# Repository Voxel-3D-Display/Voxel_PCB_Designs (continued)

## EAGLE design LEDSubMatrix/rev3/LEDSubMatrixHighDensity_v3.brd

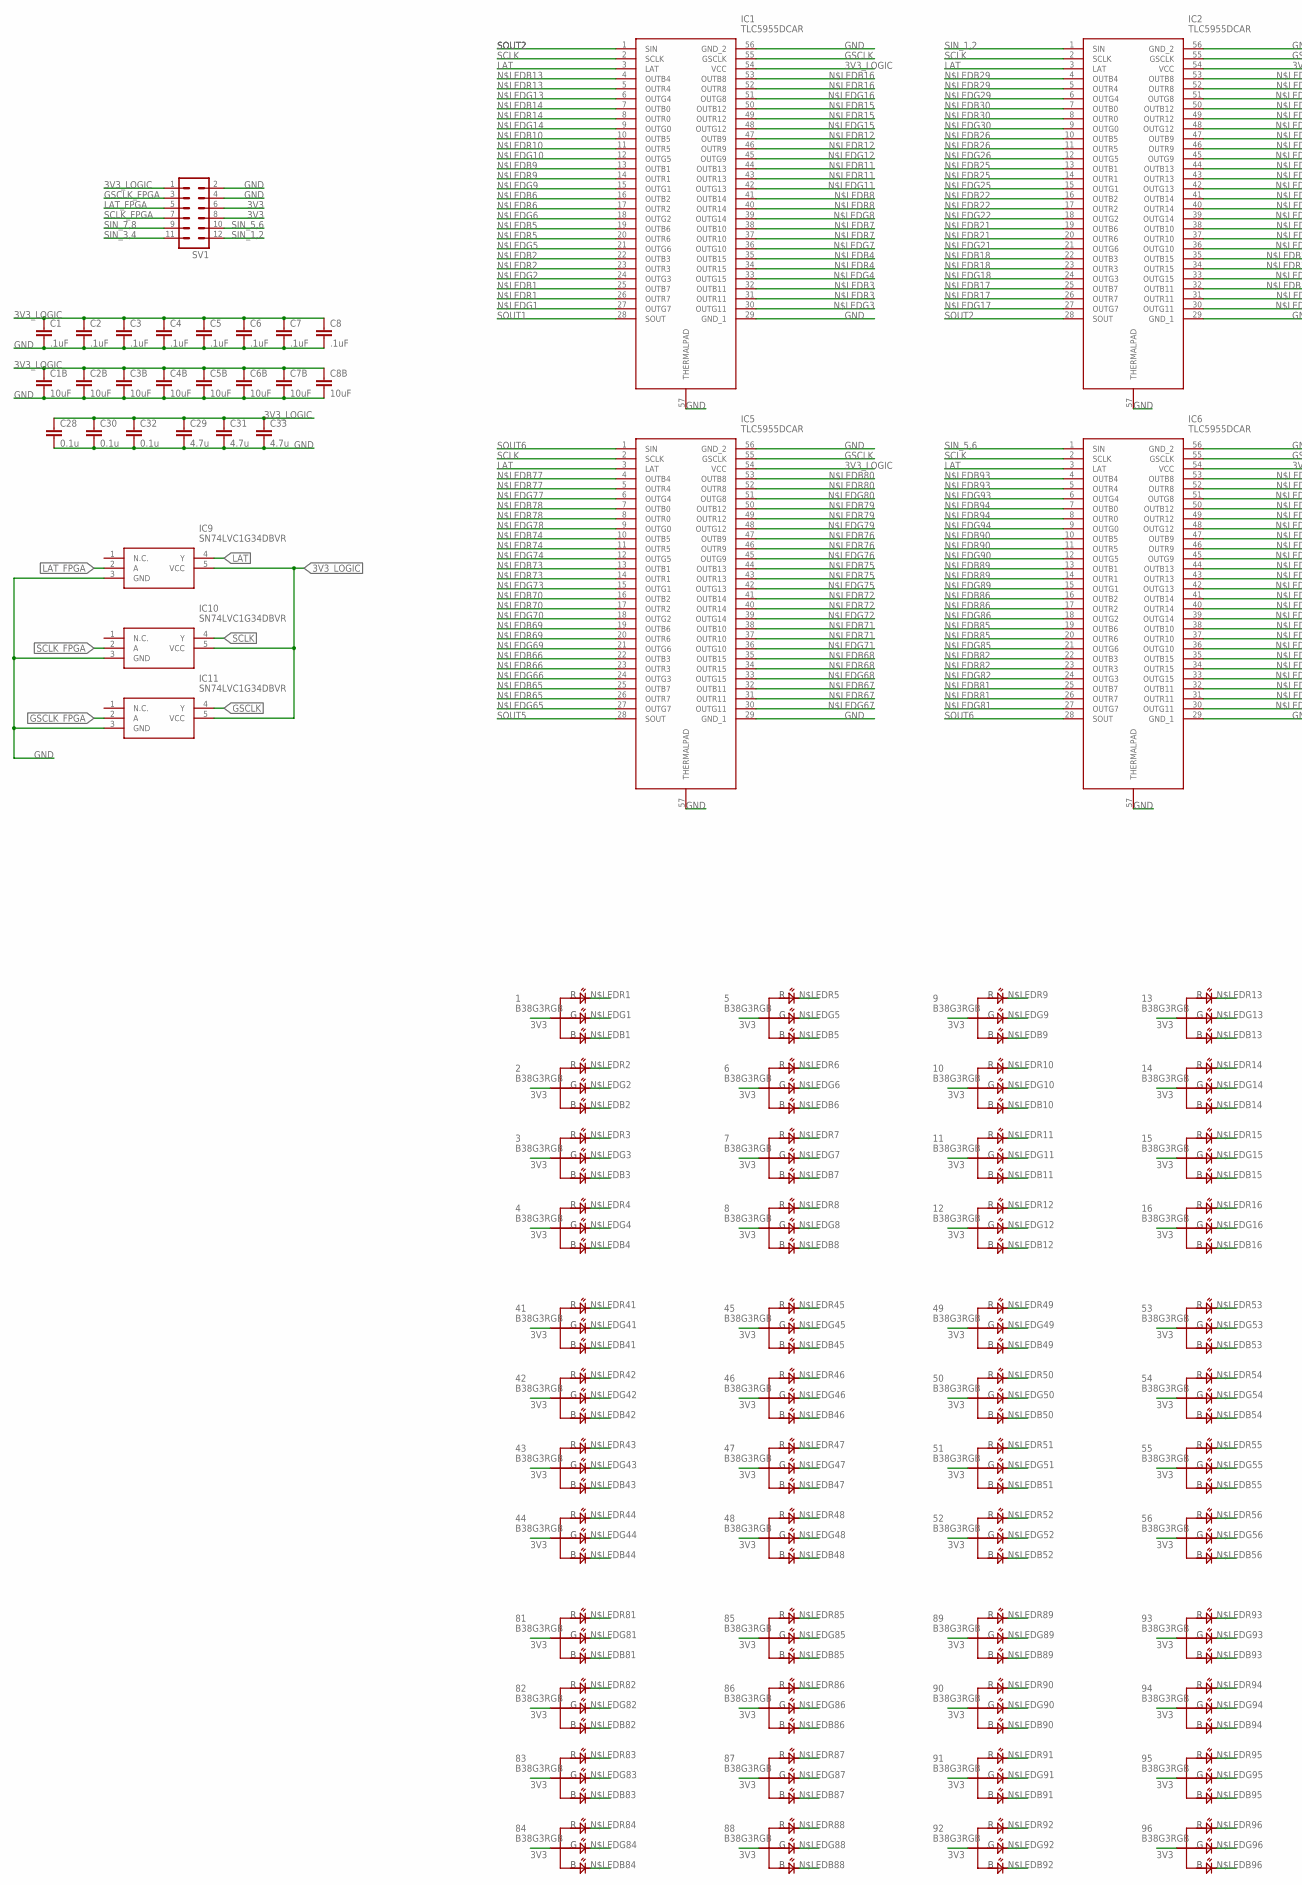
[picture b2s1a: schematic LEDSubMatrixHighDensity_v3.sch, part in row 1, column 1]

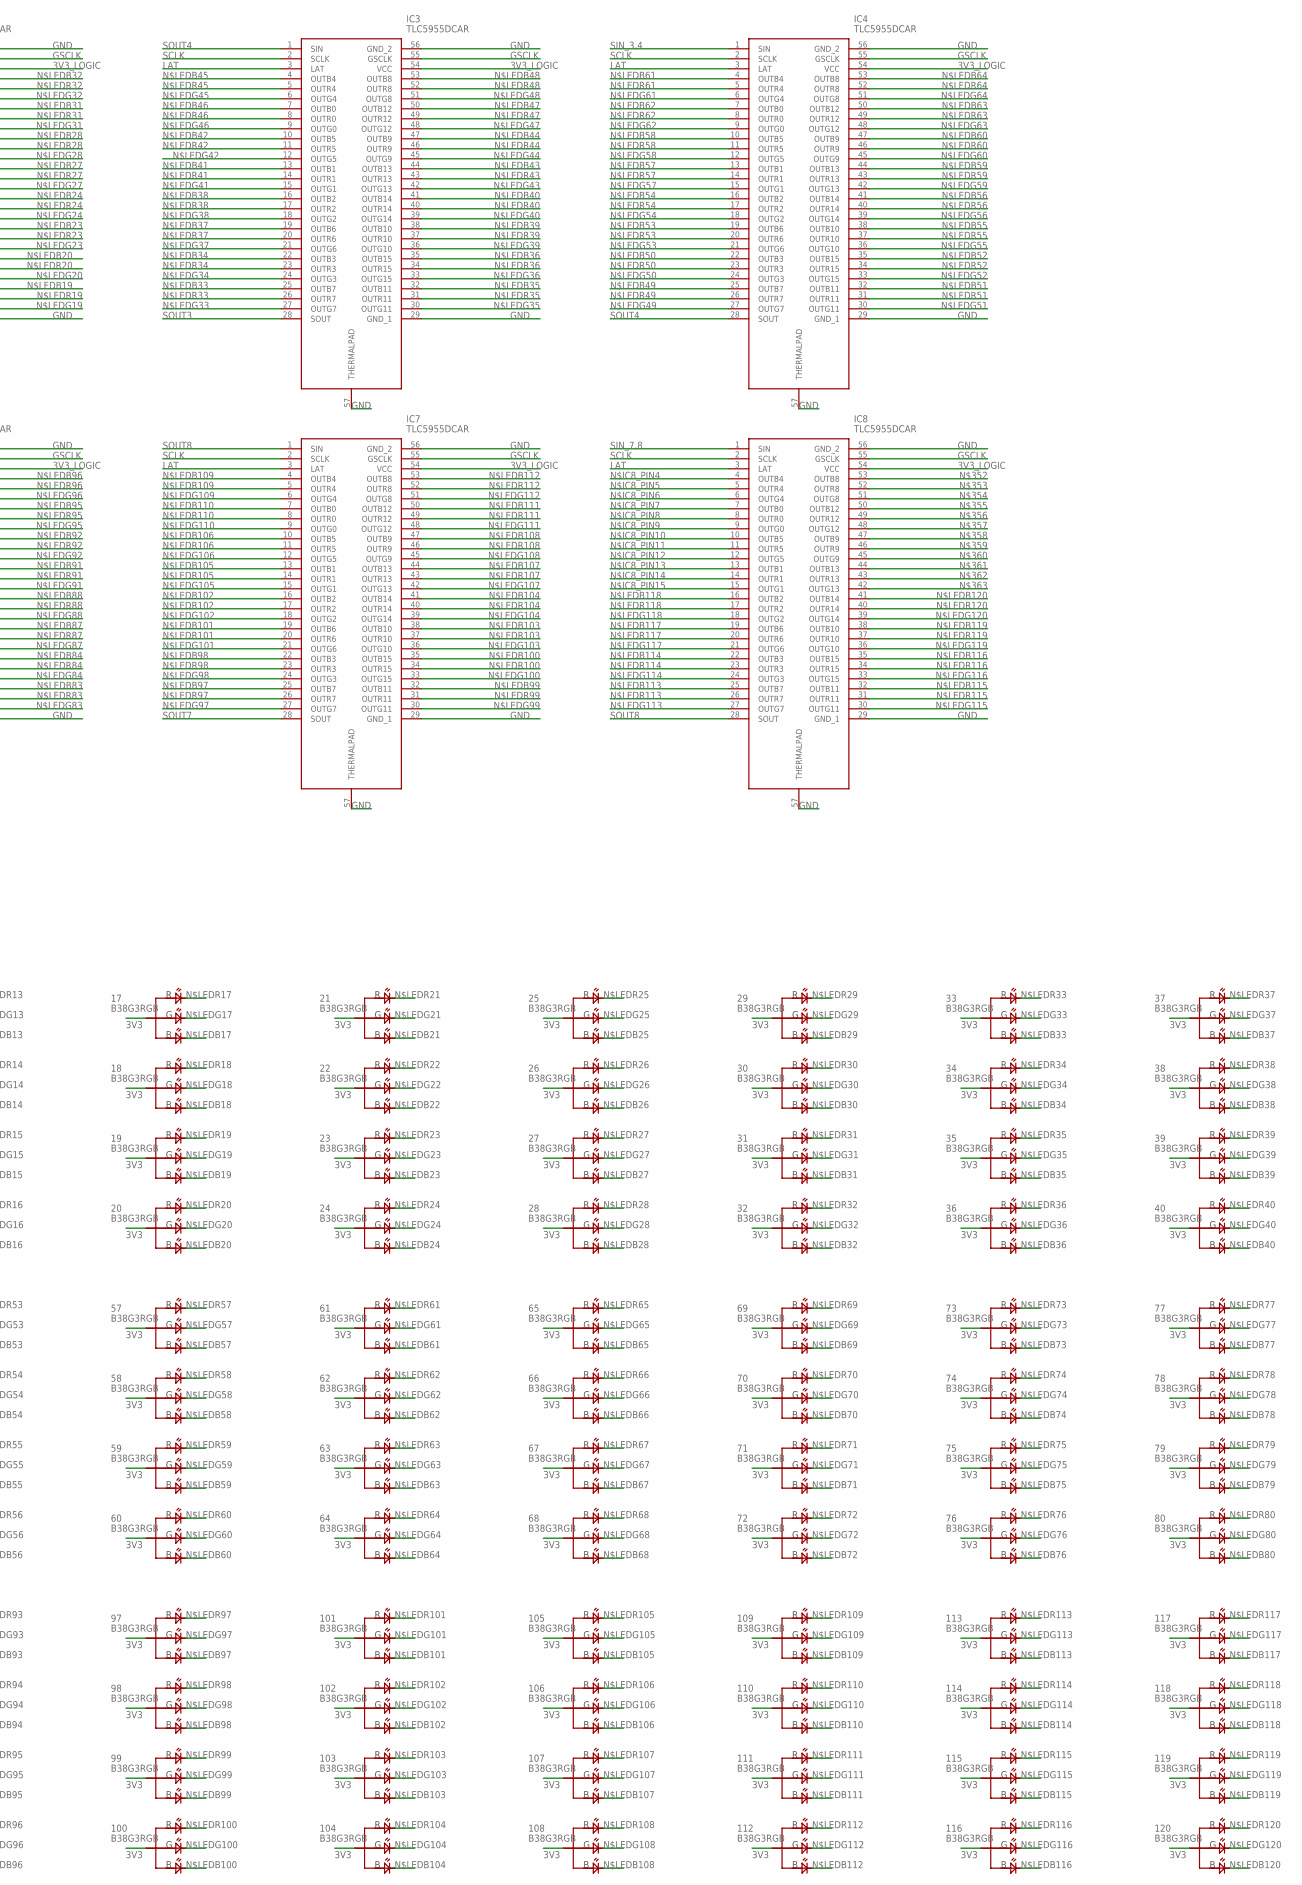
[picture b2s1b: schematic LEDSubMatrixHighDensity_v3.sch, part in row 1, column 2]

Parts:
1, 2, 3, 4, 5, 6, 7, 8, 9, 10, 11, 12, 13, 14, 15, 16, 17, 18, 19, 20, 21, 22, 23, 24, 25, 26, 27, 28, 29, 30, 31, 32, 33, 34, 35, 36, 37, 38, 39, 40, 41, 42, 43, 44, 45, 46, 47, 48, 49, 50, 51, 52, 53, 54, 55, 56, 57, 58, 59, 60, 61, 62, 63, 64, 65, 66, 67, 68, 69, 70, 71, 72, 73, 74, 75, 76, 77, 78, 79, 80, 81, 82, 83, 84, 85, 86, 87, 88, 89, 90, 91, 92, 93, 94, 95, 96, 97, 98, 99, 100, 101, 102, 103, 104, 105, 106, 107, 108, 109, 110, 111, 112, 113, 114, 115, 116, 117, 118, 119, 120: B38G3RGB
C1, C2, C3, C4, C5, C6, C7, C8: .1uF; C0402
C1B, C2B, C3B, C4B, C5B, C6B, C7B, C8B: 10uF; C0402
C28, C30, C32: 0.1u; C0402
C29, C31, C33: 4.7u; C0402
IC1, IC2, IC3, IC4, IC5, IC6, IC7, IC8: TLC5955DCAR; SOP50P810X120-57N
IC9, IC10, IC11: SN74LVC1G34DBVR; SOT95P280X145-5N
SV1: MA06-2

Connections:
3V3: 1.3 (COM), 2.3 (COM), 3.3 (COM), 4.3 (COM), 5.3 (COM), 6.3 (COM), 7.3 (COM), 8.3 (COM), 9.3 (COM), 10.3 (COM), 11.3 (COM), 12.3 (COM), 13.3 (COM), 14.3 (COM), 15.3 (COM), 16.3 (COM), 17.3 (COM), 18.3 (COM), 19.3 (COM), 20.3 (COM), 21.3 (COM), 22.3 (COM), 23.3 (COM), 24.3 (COM), 25.3 (COM), 26.3 (COM), 27.3 (COM), 28.3 (COM), 29.3 (COM), 30.3 (COM), 31.3 (COM), 32.3 (COM), 33.3 (COM), 34.3 (COM), 35.3 (COM), 36.3 (COM), 37.3 (COM), 38.3 (COM), 39.3 (COM), 40.3 (COM), 41.3 (COM), 42.3 (COM), 43.3 (COM), 44.3 (COM), 45.3 (COM), 46.3 (COM), 47.3 (COM), 48.3 (COM), 49.3 (COM), 50.3 (COM), 51.3 (COM), 52.3 (COM), 53.3 (COM), 54.3 (COM), 55.3 (COM), 56.3 (COM), 57.3 (COM), 58.3 (COM), 59.3 (COM), 60.3 (COM), 61.3 (COM), 62.3 (COM), 63.3 (COM), 64.3 (COM), 65.3 (COM), 66.3 (COM), 67.3 (COM), 68.3 (COM), 69.3 (COM), 70.3 (COM), 71.3 (COM), 72.3 (COM), 73.3 (COM), 74.3 (COM), 75.3 (COM), 76.3 (COM), 77.3 (COM), 78.3 (COM), 79.3 (COM), 80.3 (COM), 81.3 (COM), 82.3 (COM), 83.3 (COM), 84.3 (COM), 85.3 (COM), 86.3 (COM), 87.3 (COM), 88.3 (COM), 89.3 (COM), 90.3 (COM), 91.3 (COM), 92.3 (COM), 93.3 (COM), 94.3 (COM), 95.3 (COM), 96.3 (COM), 97.3 (COM), 98.3 (COM), 99.3 (COM), 100.3 (COM), 101.3 (COM), 102.3 (COM), 103.3 (COM), 104.3 (COM), 105.3 (COM), 106.3 (COM), 107.3 (COM), 108.3 (COM), 109.3 (COM), 110.3 (COM), 111.3 (COM), 112.3 (COM), 113.3 (COM), 114.3 (COM), 115.3 (COM), 116.3 (COM), 117.3 (COM), 118.3 (COM), 119.3 (COM), 120.3 (COM), SV1.6, SV1.8
3V3_LOGIC: C1.1, C1B.1, C2.1, C2B.1, C3.1, C3B.1, C4.1, C4B.1, C5.1, C5B.1, C6.1, C6B.1, C7.1, C7B.1, C8.1, C8B.1, C28.1, C29.1, C30.1, C31.1, C32.1, C33.1, IC1.54 (VCC), IC2.54 (VCC), IC3.54 (VCC), IC4.54 (VCC), IC5.54 (VCC), IC6.54 (VCC), IC7.54 (VCC), IC8.54 (VCC), IC9.5 (VCC), IC10.5 (VCC), IC11.5 (VCC), SV1.1
GND: C1.2, C1B.2, C2.2, C2B.2, C3.2, C3B.2, C4.2, C4B.2, C5.2, C5B.2, C6.2, C6B.2, C7.2, C7B.2, C8.2, C8B.2, C28.2, C29.2, C30.2, C31.2, C32.2, C33.2, IC1.29 (GND_1), IC1.56 (GND_2), IC1.57 (THERMALPAD), IC2.29 (GND_1), IC2.56 (GND_2), IC2.57 (THERMALPAD), IC3.29 (GND_1), IC3.56 (GND_2), IC3.57 (THERMALPAD), IC4.29 (GND_1), IC4.56 (GND_2), IC4.57 (THERMALPAD), IC5.29 (GND_1), IC5.56 (GND_2), IC5.57 (THERMALPAD), IC6.29 (GND_1), IC6.56 (GND_2), IC6.57 (THERMALPAD), IC7.29 (GND_1), IC7.56 (GND_2), IC7.57 (THERMALPAD), IC8.29 (GND_1), IC8.56 (GND_2), IC8.57 (THERMALPAD), IC9.3 (GND), IC10.3 (GND), IC11.3 (GND), SV1.2, SV1.4
GSCLK: IC1.55 (GSCLK), IC2.55 (GSCLK), IC3.55 (GSCLK), IC4.55 (GSCLK), IC5.55 (GSCLK), IC6.55 (GSCLK), IC7.55 (GSCLK), IC8.55 (GSCLK), IC11.4 (Y)
GSCLK_FPGA: IC11.2 (A), SV1.3
LAT: IC1.3 (LAT), IC2.3 (LAT), IC3.3 (LAT), IC4.3 (LAT), IC5.3 (LAT), IC6.3 (LAT), IC7.3 (LAT), IC8.3 (LAT), IC9.4 (Y)
LAT_FPGA: IC9.2 (A), SV1.5
N$IC8_PIN4: IC8.4 (OUTB4)
N$IC8_PIN5: IC8.5 (OUTR4)
N$IC8_PIN6: IC8.6 (OUTG4)
N$IC8_PIN7: IC8.7 (OUTB0)
N$IC8_PIN8: IC8.8 (OUTR0)
N$IC8_PIN9: IC8.9 (OUTG0)
N$IC8_PIN10: IC8.10 (OUTB5)
N$IC8_PIN11: IC8.11 (OUTR5)
N$IC8_PIN12: IC8.12 (OUTG5)
N$IC8_PIN13: IC8.13 (OUTB1)
N$IC8_PIN14: IC8.14 (OUTR1)
N$IC8_PIN15: IC8.15 (OUTG1)
N$LEDB1: 1.2 (BLUE), IC1.25 (OUTB7)
N$LEDB2: 2.2 (BLUE), IC1.22 (OUTB3)
N$LEDB3: 3.2 (BLUE), IC1.32 (OUTB11)
N$LEDB4: 4.2 (BLUE), IC1.35 (OUTB15)
N$LEDB5: 5.2 (BLUE), IC1.19 (OUTB6)
N$LEDB6: 6.2 (BLUE), IC1.16 (OUTB2)
N$LEDB7: 7.2 (BLUE), IC1.38 (OUTB10)
N$LEDB8: 8.2 (BLUE), IC1.41 (OUTB14)
N$LEDB9: 9.2 (BLUE), IC1.13 (OUTB1)
N$LEDB10: 10.2 (BLUE), IC1.10 (OUTB5)
N$LEDB11: 11.2 (BLUE), IC1.44 (OUTB13)
N$LEDB12: 12.2 (BLUE), IC1.47 (OUTB9)
N$LEDB13: 13.2 (BLUE), IC1.4 (OUTB4)
N$LEDB14: 14.2 (BLUE), IC1.7 (OUTB0)
N$LEDB15: 15.2 (BLUE), IC1.50 (OUTB12)
N$LEDB16: 16.2 (BLUE), IC1.53 (OUTB8)
N$LEDB17: 17.2 (BLUE), IC2.25 (OUTB7)
N$LEDB18: 18.2 (BLUE), IC2.22 (OUTB3)
N$LEDB19: 19.2 (BLUE), IC2.32 (OUTB11)
N$LEDB20: 20.2 (BLUE), IC2.35 (OUTB15)
N$LEDB21: 21.2 (BLUE), IC2.19 (OUTB6)
N$LEDB22: 22.2 (BLUE), IC2.16 (OUTB2)
N$LEDB23: 23.2 (BLUE), IC2.38 (OUTB10)
N$LEDB24: 24.2 (BLUE), IC2.41 (OUTB14)
N$LEDB25: 25.2 (BLUE), IC2.13 (OUTB1)
N$LEDB26: 26.2 (BLUE), IC2.10 (OUTB5)
N$LEDB27: 27.2 (BLUE), IC2.44 (OUTB13)
N$LEDB28: 28.2 (BLUE), IC2.47 (OUTB9)
N$LEDB29: 29.2 (BLUE), IC2.4 (OUTB4)
N$LEDB30: 30.2 (BLUE), IC2.7 (OUTB0)
N$LEDB31: 31.2 (BLUE), IC2.50 (OUTB12)
N$LEDB32: 32.2 (BLUE), IC2.53 (OUTB8)
N$LEDB33: 33.2 (BLUE), IC3.25 (OUTB7)
N$LEDB34: 34.2 (BLUE), IC3.22 (OUTB3)
N$LEDB35: 35.2 (BLUE), IC3.32 (OUTB11)
N$LEDB36: 36.2 (BLUE), IC3.35 (OUTB15)
N$LEDB37: 37.2 (BLUE), IC3.19 (OUTB6)
N$LEDB38: 38.2 (BLUE), IC3.16 (OUTB2)
N$LEDB39: 39.2 (BLUE), IC3.38 (OUTB10)
N$LEDB40: 40.2 (BLUE), IC3.41 (OUTB14)
N$LEDB41: 41.2 (BLUE), IC3.13 (OUTB1)
N$LEDB42: 42.2 (BLUE), IC3.10 (OUTB5)
N$LEDB43: 43.2 (BLUE), IC3.44 (OUTB13)
N$LEDB44: 44.2 (BLUE), IC3.47 (OUTB9)
N$LEDB45: 45.2 (BLUE), IC3.4 (OUTB4)
N$LEDB46: 46.2 (BLUE), IC3.7 (OUTB0)
N$LEDB47: 47.2 (BLUE), IC3.50 (OUTB12)
N$LEDB48: 48.2 (BLUE), IC3.53 (OUTB8)
N$LEDB49: 49.2 (BLUE), IC4.25 (OUTB7)
N$LEDB50: 50.2 (BLUE), IC4.22 (OUTB3)
N$LEDB51: 51.2 (BLUE), IC4.32 (OUTB11)
N$LEDB52: 52.2 (BLUE), IC4.35 (OUTB15)
N$LEDB53: 53.2 (BLUE), IC4.19 (OUTB6)
N$LEDB54: 54.2 (BLUE), IC4.16 (OUTB2)
N$LEDB55: 55.2 (BLUE), IC4.38 (OUTB10)
N$LEDB56: 56.2 (BLUE), IC4.41 (OUTB14)
N$LEDB57: 57.2 (BLUE), IC4.13 (OUTB1)
N$LEDB58: 58.2 (BLUE), IC4.10 (OUTB5)
N$LEDB59: 59.2 (BLUE), IC4.44 (OUTB13)
N$LEDB60: 60.2 (BLUE), IC4.47 (OUTB9)
N$LEDB61: 61.2 (BLUE), IC4.4 (OUTB4)
N$LEDB62: 62.2 (BLUE), IC4.7 (OUTB0)
N$LEDB63: 63.2 (BLUE), IC4.50 (OUTB12)
N$LEDB64: 64.2 (BLUE), IC4.53 (OUTB8)
N$LEDB65: 65.2 (BLUE), IC5.25 (OUTB7)
N$LEDB66: 66.2 (BLUE), IC5.22 (OUTB3)
N$LEDB67: 67.2 (BLUE), IC5.32 (OUTB11)
N$LEDB68: 68.2 (BLUE), IC5.35 (OUTB15)
N$LEDB69: 69.2 (BLUE), IC5.19 (OUTB6)
N$LEDB70: 70.2 (BLUE), IC5.16 (OUTB2)
N$LEDB71: 71.2 (BLUE), IC5.38 (OUTB10)
N$LEDB72: 72.2 (BLUE), IC5.41 (OUTB14)
N$LEDB73: 73.2 (BLUE), IC5.13 (OUTB1)
N$LEDB74: 74.2 (BLUE), IC5.10 (OUTB5)
N$LEDB75: 75.2 (BLUE), IC5.44 (OUTB13)
N$LEDB76: 76.2 (BLUE), IC5.47 (OUTB9)
N$LEDB77: 77.2 (BLUE), IC5.4 (OUTB4)
N$LEDB78: 78.2 (BLUE), IC5.7 (OUTB0)
N$LEDB79: 79.2 (BLUE), IC5.50 (OUTB12)
N$LEDB80: 80.2 (BLUE), IC5.53 (OUTB8)
N$LEDB81: 81.2 (BLUE), IC6.25 (OUTB7)
N$LEDB82: 82.2 (BLUE), IC6.22 (OUTB3)
N$LEDB83: 83.2 (BLUE), IC6.32 (OUTB11)
N$LEDB84: 84.2 (BLUE), IC6.35 (OUTB15)
N$LEDB85: 85.2 (BLUE), IC6.19 (OUTB6)
N$LEDB86: 86.2 (BLUE), IC6.16 (OUTB2)
N$LEDB87: 87.2 (BLUE), IC6.38 (OUTB10)
N$LEDB88: 88.2 (BLUE), IC6.41 (OUTB14)
N$LEDB89: 89.2 (BLUE), IC6.13 (OUTB1)
N$LEDB90: 90.2 (BLUE), IC6.10 (OUTB5)
N$LEDB91: 91.2 (BLUE), IC6.44 (OUTB13)
N$LEDB92: 92.2 (BLUE), IC6.47 (OUTB9)
N$LEDB93: 93.2 (BLUE), IC6.4 (OUTB4)
N$LEDB94: 94.2 (BLUE), IC6.7 (OUTB0)
N$LEDB95: 95.2 (BLUE), IC6.50 (OUTB12)
N$LEDB96: 96.2 (BLUE), IC6.53 (OUTB8)
N$LEDB97: 97.2 (BLUE), IC7.25 (OUTB7)
N$LEDB98: 98.2 (BLUE), IC7.22 (OUTB3)
N$LEDB99: 99.2 (BLUE), IC7.32 (OUTB11)
N$LEDB100: 100.2 (BLUE), IC7.35 (OUTB15)
N$LEDB101: 101.2 (BLUE), IC7.19 (OUTB6)
N$LEDB102: 102.2 (BLUE), IC7.16 (OUTB2)
N$LEDB103: 103.2 (BLUE), IC7.38 (OUTB10)
N$LEDB104: 104.2 (BLUE), IC7.41 (OUTB14)
N$LEDB105: 105.2 (BLUE), IC7.13 (OUTB1)
N$LEDB106: 106.2 (BLUE), IC7.10 (OUTB5)
N$LEDB107: 107.2 (BLUE), IC7.44 (OUTB13)
N$LEDB108: 108.2 (BLUE), IC7.47 (OUTB9)
N$LEDB109: 109.2 (BLUE), IC7.4 (OUTB4)
N$LEDB110: 110.2 (BLUE), IC7.7 (OUTB0)
N$LEDB111: 111.2 (BLUE), IC7.50 (OUTB12)
N$LEDB112: 112.2 (BLUE), IC7.53 (OUTB8)
N$LEDB113: 113.2 (BLUE), IC8.25 (OUTB7)
N$LEDB114: 114.2 (BLUE), IC8.22 (OUTB3)
N$LEDB115: 115.2 (BLUE), IC8.32 (OUTB11)
N$LEDB116: 116.2 (BLUE), IC8.35 (OUTB15)
N$LEDB117: 117.2 (BLUE), IC8.19 (OUTB6)
N$LEDB118: 118.2 (BLUE), IC8.16 (OUTB2)
N$LEDB119: 119.2 (BLUE), IC8.38 (OUTB10)
N$LEDB120: 120.2 (BLUE), IC8.41 (OUTB14)
N$LEDG1: 1.1 (GREEN), IC1.27 (OUTG7)
N$LEDG2: 2.1 (GREEN), IC1.24 (OUTG3)
N$LEDG3: 3.1 (GREEN), IC1.30 (OUTG11)
N$LEDG4: 4.1 (GREEN), IC1.33 (OUTG15)
N$LEDG5: 5.1 (GREEN), IC1.21 (OUTG6)
N$LEDG6: 6.1 (GREEN), IC1.18 (OUTG2)
N$LEDG7: 7.1 (GREEN), IC1.36 (OUTG10)
N$LEDG8: 8.1 (GREEN), IC1.39 (OUTG14)
N$LEDG9: 9.1 (GREEN), IC1.15 (OUTG1)
N$LEDG10: 10.1 (GREEN), IC1.12 (OUTG5)
N$LEDG11: 11.1 (GREEN), IC1.42 (OUTG13)
N$LEDG12: 12.1 (GREEN), IC1.45 (OUTG9)
N$LEDG13: 13.1 (GREEN), IC1.6 (OUTG4)
N$LEDG14: 14.1 (GREEN), IC1.9 (OUTG0)
N$LEDG15: 15.1 (GREEN), IC1.48 (OUTG12)
N$LEDG16: 16.1 (GREEN), IC1.51 (OUTG8)
N$LEDG17: 17.1 (GREEN), IC2.27 (OUTG7)
N$LEDG18: 18.1 (GREEN), IC2.24 (OUTG3)
N$LEDG19: 19.1 (GREEN), IC2.30 (OUTG11)
N$LEDG20: 20.1 (GREEN), IC2.33 (OUTG15)
N$LEDG21: 21.1 (GREEN), IC2.21 (OUTG6)
N$LEDG22: 22.1 (GREEN), IC2.18 (OUTG2)
N$LEDG23: 23.1 (GREEN), IC2.36 (OUTG10)
N$LEDG24: 24.1 (GREEN), IC2.39 (OUTG14)
N$LEDG25: 25.1 (GREEN), IC2.15 (OUTG1)
N$LEDG26: 26.1 (GREEN), IC2.12 (OUTG5)
N$LEDG27: 27.1 (GREEN), IC2.42 (OUTG13)
N$LEDG28: 28.1 (GREEN), IC2.45 (OUTG9)
N$LEDG29: 29.1 (GREEN), IC2.6 (OUTG4)
N$LEDG30: 30.1 (GREEN), IC2.9 (OUTG0)
N$LEDG31: 31.1 (GREEN), IC2.48 (OUTG12)
N$LEDG32: 32.1 (GREEN), IC2.51 (OUTG8)
N$LEDG33: 33.1 (GREEN), IC3.27 (OUTG7)
N$LEDG34: 34.1 (GREEN), IC3.24 (OUTG3)
N$LEDG35: 35.1 (GREEN), IC3.30 (OUTG11)
N$LEDG36: 36.1 (GREEN), IC3.33 (OUTG15)
N$LEDG37: 37.1 (GREEN), IC3.21 (OUTG6)
N$LEDG38: 38.1 (GREEN), IC3.18 (OUTG2)
N$LEDG39: 39.1 (GREEN), IC3.36 (OUTG10)
N$LEDG40: 40.1 (GREEN), IC3.39 (OUTG14)
N$LEDG41: 41.1 (GREEN), IC3.15 (OUTG1)
N$LEDG42: 42.1 (GREEN), IC3.12 (OUTG5)
N$LEDG43: 43.1 (GREEN), IC3.42 (OUTG13)
N$LEDG44: 44.1 (GREEN), IC3.45 (OUTG9)
N$LEDG45: 45.1 (GREEN), IC3.6 (OUTG4)
N$LEDG46: 46.1 (GREEN), IC3.9 (OUTG0)
N$LEDG47: 47.1 (GREEN), IC3.48 (OUTG12)
N$LEDG48: 48.1 (GREEN), IC3.51 (OUTG8)
N$LEDG49: 49.1 (GREEN), IC4.27 (OUTG7)
N$LEDG50: 50.1 (GREEN), IC4.24 (OUTG3)
N$LEDG51: 51.1 (GREEN), IC4.30 (OUTG11)
N$LEDG52: 52.1 (GREEN), IC4.33 (OUTG15)
N$LEDG53: 53.1 (GREEN), IC4.21 (OUTG6)
N$LEDG54: 54.1 (GREEN), IC4.18 (OUTG2)
N$LEDG55: 55.1 (GREEN), IC4.36 (OUTG10)
N$LEDG56: 56.1 (GREEN), IC4.39 (OUTG14)
N$LEDG57: 57.1 (GREEN), IC4.15 (OUTG1)
N$LEDG58: 58.1 (GREEN), IC4.12 (OUTG5)
N$LEDG59: 59.1 (GREEN), IC4.42 (OUTG13)
N$LEDG60: 60.1 (GREEN), IC4.45 (OUTG9)
N$LEDG61: 61.1 (GREEN), IC4.6 (OUTG4)
N$LEDG62: 62.1 (GREEN), IC4.9 (OUTG0)
N$LEDG63: 63.1 (GREEN), IC4.48 (OUTG12)
N$LEDG64: 64.1 (GREEN), IC4.51 (OUTG8)
N$LEDG65: 65.1 (GREEN), IC5.27 (OUTG7)
N$LEDG66: 66.1 (GREEN), IC5.24 (OUTG3)
N$LEDG67: 67.1 (GREEN), IC5.30 (OUTG11)
N$LEDG68: 68.1 (GREEN), IC5.33 (OUTG15)
N$LEDG69: 69.1 (GREEN), IC5.21 (OUTG6)
N$LEDG70: 70.1 (GREEN), IC5.18 (OUTG2)
N$LEDG71: 71.1 (GREEN), IC5.36 (OUTG10)
N$LEDG72: 72.1 (GREEN), IC5.39 (OUTG14)
N$LEDG73: 73.1 (GREEN), IC5.15 (OUTG1)
N$LEDG74: 74.1 (GREEN), IC5.12 (OUTG5)
N$LEDG75: 75.1 (GREEN), IC5.42 (OUTG13)
N$LEDG76: 76.1 (GREEN), IC5.45 (OUTG9)
N$LEDG77: 77.1 (GREEN), IC5.6 (OUTG4)
N$LEDG78: 78.1 (GREEN), IC5.9 (OUTG0)
N$LEDG79: 79.1 (GREEN), IC5.48 (OUTG12)
N$LEDG80: 80.1 (GREEN), IC5.51 (OUTG8)
N$LEDG81: 81.1 (GREEN), IC6.27 (OUTG7)
N$LEDG82: 82.1 (GREEN), IC6.24 (OUTG3)
N$LEDG83: 83.1 (GREEN), IC6.30 (OUTG11)
N$LEDG84: 84.1 (GREEN), IC6.33 (OUTG15)
N$LEDG85: 85.1 (GREEN), IC6.21 (OUTG6)
N$LEDG86: 86.1 (GREEN), IC6.18 (OUTG2)
N$LEDG87: 87.1 (GREEN), IC6.36 (OUTG10)
N$LEDG88: 88.1 (GREEN), IC6.39 (OUTG14)
N$LEDG89: 89.1 (GREEN), IC6.15 (OUTG1)
N$LEDG90: 90.1 (GREEN), IC6.12 (OUTG5)
N$LEDG91: 91.1 (GREEN), IC6.42 (OUTG13)
N$LEDG92: 92.1 (GREEN), IC6.45 (OUTG9)
N$LEDG93: 93.1 (GREEN), IC6.6 (OUTG4)
N$LEDG94: 94.1 (GREEN), IC6.9 (OUTG0)
N$LEDG95: 95.1 (GREEN), IC6.48 (OUTG12)
N$LEDG96: 96.1 (GREEN), IC6.51 (OUTG8)
N$LEDG97: 97.1 (GREEN), IC7.27 (OUTG7)
N$LEDG98: 98.1 (GREEN), IC7.24 (OUTG3)
N$LEDG99: 99.1 (GREEN), IC7.30 (OUTG11)
N$LEDG100: 100.1 (GREEN), IC7.33 (OUTG15)
N$LEDG101: 101.1 (GREEN), IC7.21 (OUTG6)
N$LEDG102: 102.1 (GREEN), IC7.18 (OUTG2)
N$LEDG103: 103.1 (GREEN), IC7.36 (OUTG10)
N$LEDG104: 104.1 (GREEN), IC7.39 (OUTG14)
N$LEDG105: 105.1 (GREEN), IC7.15 (OUTG1)
N$LEDG106: 106.1 (GREEN), IC7.12 (OUTG5)
N$LEDG107: 107.1 (GREEN), IC7.42 (OUTG13)
N$LEDG108: 108.1 (GREEN), IC7.45 (OUTG9)
N$LEDG109: 109.1 (GREEN), IC7.6 (OUTG4)
N$LEDG110: 110.1 (GREEN), IC7.9 (OUTG0)
N$LEDG111: 111.1 (GREEN), IC7.48 (OUTG12)
N$LEDG112: 112.1 (GREEN), IC7.51 (OUTG8)
N$LEDG113: 113.1 (GREEN), IC8.27 (OUTG7)
N$LEDG114: 114.1 (GREEN), IC8.24 (OUTG3)
N$LEDG115: 115.1 (GREEN), IC8.30 (OUTG11)
N$LEDG116: 116.1 (GREEN), IC8.33 (OUTG15)
N$LEDG117: 117.1 (GREEN), IC8.21 (OUTG6)
N$LEDG118: 118.1 (GREEN), IC8.18 (OUTG2)
N$LEDG119: 119.1 (GREEN), IC8.36 (OUTG10)
N$LEDG120: 120.1 (GREEN), IC8.39 (OUTG14)
N$LEDR1: 1.4 (RED), IC1.26 (OUTR7)
N$LEDR2: 2.4 (RED), IC1.23 (OUTR3)
N$LEDR3: 3.4 (RED), IC1.31 (OUTR11)
N$LEDR4: 4.4 (RED), IC1.34 (OUTR15)
N$LEDR5: 5.4 (RED), IC1.20 (OUTR6)
N$LEDR6: 6.4 (RED), IC1.17 (OUTR2)
N$LEDR7: 7.4 (RED), IC1.37 (OUTR10)
N$LEDR8: 8.4 (RED), IC1.40 (OUTR14)
N$LEDR9: 9.4 (RED), IC1.14 (OUTR1)
N$LEDR10: 10.4 (RED), IC1.11 (OUTR5)
N$LEDR11: 11.4 (RED), IC1.43 (OUTR13)
N$LEDR12: 12.4 (RED), IC1.46 (OUTR9)
N$LEDR13: 13.4 (RED), IC1.5 (OUTR4)
N$LEDR14: 14.4 (RED), IC1.8 (OUTR0)
N$LEDR15: 15.4 (RED), IC1.49 (OUTR12)
N$LEDR16: 16.4 (RED), IC1.52 (OUTR8)
N$LEDR17: 17.4 (RED), IC2.26 (OUTR7)
N$LEDR18: 18.4 (RED), IC2.23 (OUTR3)
N$LEDR19: 19.4 (RED), IC2.31 (OUTR11)
N$LEDR20: 20.4 (RED), IC2.34 (OUTR15)
N$LEDR21: 21.4 (RED), IC2.20 (OUTR6)
N$LEDR22: 22.4 (RED), IC2.17 (OUTR2)
N$LEDR23: 23.4 (RED), IC2.37 (OUTR10)
N$LEDR24: 24.4 (RED), IC2.40 (OUTR14)
N$LEDR25: 25.4 (RED), IC2.14 (OUTR1)
N$LEDR26: 26.4 (RED), IC2.11 (OUTR5)
N$LEDR27: 27.4 (RED), IC2.43 (OUTR13)
N$LEDR28: 28.4 (RED), IC2.46 (OUTR9)
N$LEDR29: 29.4 (RED), IC2.5 (OUTR4)
N$LEDR30: 30.4 (RED), IC2.8 (OUTR0)
N$LEDR31: 31.4 (RED), IC2.49 (OUTR12)
N$LEDR32: 32.4 (RED), IC2.52 (OUTR8)
N$LEDR33: 33.4 (RED), IC3.26 (OUTR7)
N$LEDR34: 34.4 (RED), IC3.23 (OUTR3)
N$LEDR35: 35.4 (RED), IC3.31 (OUTR11)
N$LEDR36: 36.4 (RED), IC3.34 (OUTR15)
N$LEDR37: 37.4 (RED), IC3.20 (OUTR6)
N$LEDR38: 38.4 (RED), IC3.17 (OUTR2)
N$LEDR39: 39.4 (RED), IC3.37 (OUTR10)
N$LEDR40: 40.4 (RED), IC3.40 (OUTR14)
N$LEDR41: 41.4 (RED), IC3.14 (OUTR1)
N$LEDR42: 42.4 (RED), IC3.11 (OUTR5)
N$LEDR43: 43.4 (RED), IC3.43 (OUTR13)
N$LEDR44: 44.4 (RED), IC3.46 (OUTR9)
N$LEDR45: 45.4 (RED), IC3.5 (OUTR4)
N$LEDR46: 46.4 (RED), IC3.8 (OUTR0)
N$LEDR47: 47.4 (RED), IC3.49 (OUTR12)
N$LEDR48: 48.4 (RED), IC3.52 (OUTR8)
N$LEDR49: 49.4 (RED), IC4.26 (OUTR7)
N$LEDR50: 50.4 (RED), IC4.23 (OUTR3)
N$LEDR51: 51.4 (RED), IC4.31 (OUTR11)
N$LEDR52: 52.4 (RED), IC4.34 (OUTR15)
N$LEDR53: 53.4 (RED), IC4.20 (OUTR6)
N$LEDR54: 54.4 (RED), IC4.17 (OUTR2)
N$LEDR55: 55.4 (RED), IC4.37 (OUTR10)
N$LEDR56: 56.4 (RED), IC4.40 (OUTR14)
N$LEDR57: 57.4 (RED), IC4.14 (OUTR1)
N$LEDR58: 58.4 (RED), IC4.11 (OUTR5)
N$LEDR59: 59.4 (RED), IC4.43 (OUTR13)
N$LEDR60: 60.4 (RED), IC4.46 (OUTR9)
N$LEDR61: 61.4 (RED), IC4.5 (OUTR4)
N$LEDR62: 62.4 (RED), IC4.8 (OUTR0)
N$LEDR63: 63.4 (RED), IC4.49 (OUTR12)
N$LEDR64: 64.4 (RED), IC4.52 (OUTR8)
N$LEDR65: 65.4 (RED), IC5.26 (OUTR7)
N$LEDR66: 66.4 (RED), IC5.23 (OUTR3)
N$LEDR67: 67.4 (RED), IC5.31 (OUTR11)
N$LEDR68: 68.4 (RED), IC5.34 (OUTR15)
N$LEDR69: 69.4 (RED), IC5.20 (OUTR6)
N$LEDR70: 70.4 (RED), IC5.17 (OUTR2)
N$LEDR71: 71.4 (RED), IC5.37 (OUTR10)
N$LEDR72: 72.4 (RED), IC5.40 (OUTR14)
N$LEDR73: 73.4 (RED), IC5.14 (OUTR1)
N$LEDR74: 74.4 (RED), IC5.11 (OUTR5)
N$LEDR75: 75.4 (RED), IC5.43 (OUTR13)
N$LEDR76: 76.4 (RED), IC5.46 (OUTR9)
N$LEDR77: 77.4 (RED), IC5.5 (OUTR4)
N$LEDR78: 78.4 (RED), IC5.8 (OUTR0)
N$LEDR79: 79.4 (RED), IC5.49 (OUTR12)
N$LEDR80: 80.4 (RED), IC5.52 (OUTR8)
N$LEDR81: 81.4 (RED), IC6.26 (OUTR7)
N$LEDR82: 82.4 (RED), IC6.23 (OUTR3)
N$LEDR83: 83.4 (RED), IC6.31 (OUTR11)
N$LEDR84: 84.4 (RED), IC6.34 (OUTR15)
N$LEDR85: 85.4 (RED), IC6.20 (OUTR6)
N$LEDR86: 86.4 (RED), IC6.17 (OUTR2)
N$LEDR87: 87.4 (RED), IC6.37 (OUTR10)
N$LEDR88: 88.4 (RED), IC6.40 (OUTR14)
N$LEDR89: 89.4 (RED), IC6.14 (OUTR1)
N$LEDR90: 90.4 (RED), IC6.11 (OUTR5)
N$LEDR91: 91.4 (RED), IC6.43 (OUTR13)
N$LEDR92: 92.4 (RED), IC6.46 (OUTR9)
N$LEDR93: 93.4 (RED), IC6.5 (OUTR4)
N$LEDR94: 94.4 (RED), IC6.8 (OUTR0)
N$LEDR95: 95.4 (RED), IC6.49 (OUTR12)
N$LEDR96: 96.4 (RED), IC6.52 (OUTR8)
N$LEDR97: 97.4 (RED), IC7.26 (OUTR7)
N$LEDR98: 98.4 (RED), IC7.23 (OUTR3)
N$LEDR99: 99.4 (RED), IC7.31 (OUTR11)
N$LEDR100: 100.4 (RED), IC7.34 (OUTR15)
N$LEDR101: 101.4 (RED), IC7.20 (OUTR6)
N$LEDR102: 102.4 (RED), IC7.17 (OUTR2)
N$LEDR103: 103.4 (RED), IC7.37 (OUTR10)
N$LEDR104: 104.4 (RED), IC7.40 (OUTR14)
N$LEDR105: 105.4 (RED), IC7.14 (OUTR1)
N$LEDR106: 106.4 (RED), IC7.11 (OUTR5)
N$LEDR107: 107.4 (RED), IC7.43 (OUTR13)
N$LEDR108: 108.4 (RED), IC7.46 (OUTR9)
N$LEDR109: 109.4 (RED), IC7.5 (OUTR4)
N$LEDR110: 110.4 (RED), IC7.8 (OUTR0)
N$LEDR111: 111.4 (RED), IC7.49 (OUTR12)
N$LEDR112: 112.4 (RED), IC7.52 (OUTR8)
N$LEDR113: 113.4 (RED), IC8.26 (OUTR7)
N$LEDR114: 114.4 (RED), IC8.23 (OUTR3)
N$LEDR115: 115.4 (RED), IC8.31 (OUTR11)
N$LEDR116: 116.4 (RED), IC8.34 (OUTR15)
N$LEDR117: 117.4 (RED), IC8.20 (OUTR6)
N$LEDR118: 118.4 (RED), IC8.17 (OUTR2)
N$LEDR119: 119.4 (RED), IC8.37 (OUTR10)
N$LEDR120: 120.4 (RED), IC8.40 (OUTR14)
SCLK: IC1.2 (SCLK), IC2.2 (SCLK), IC3.2 (SCLK), IC4.2 (SCLK), IC5.2 (SCLK), IC6.2 (SCLK), IC7.2 (SCLK), IC8.2 (SCLK), IC10.4 (Y)
SCLK_FPGA: IC10.2 (A), SV1.7
SIN_1,2: IC2.1 (SIN), SV1.12
SIN_3,4: IC4.1 (SIN), SV1.11
SIN_5,6: IC6.1 (SIN), SV1.10
SIN_7,8: IC8.1 (SIN), SV1.9
SOUT1: IC1.28 (SOUT)
SOUT2: IC1.1 (SIN), IC2.28 (SOUT)
SOUT3: IC3.28 (SOUT)
SOUT4: IC3.1 (SIN), IC4.28 (SOUT)
SOUT5: IC5.28 (SOUT)
SOUT6: IC5.1 (SIN), IC6.28 (SOUT)
SOUT7: IC7.28 (SOUT)
SOUT8: IC7.1 (SIN), IC8.28 (SOUT)

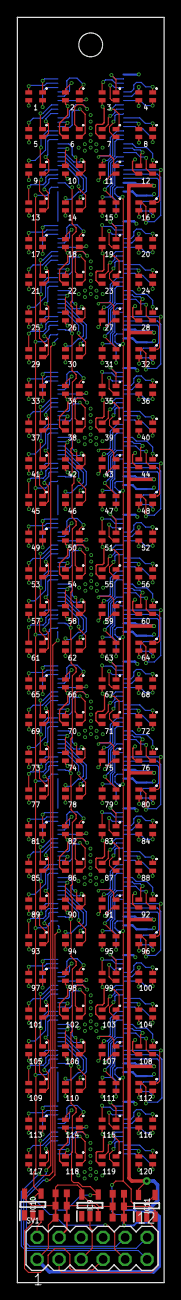
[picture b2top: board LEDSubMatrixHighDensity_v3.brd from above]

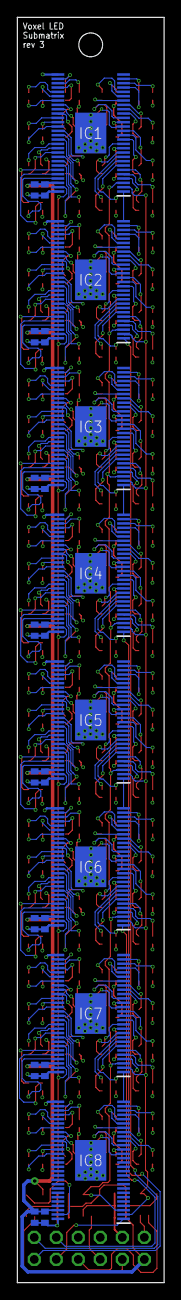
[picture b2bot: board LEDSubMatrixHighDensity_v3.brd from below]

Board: 4 copper layers, 16.9 x 146.0 mm, 154 parts (24 on the bottom side), 377 nets.
